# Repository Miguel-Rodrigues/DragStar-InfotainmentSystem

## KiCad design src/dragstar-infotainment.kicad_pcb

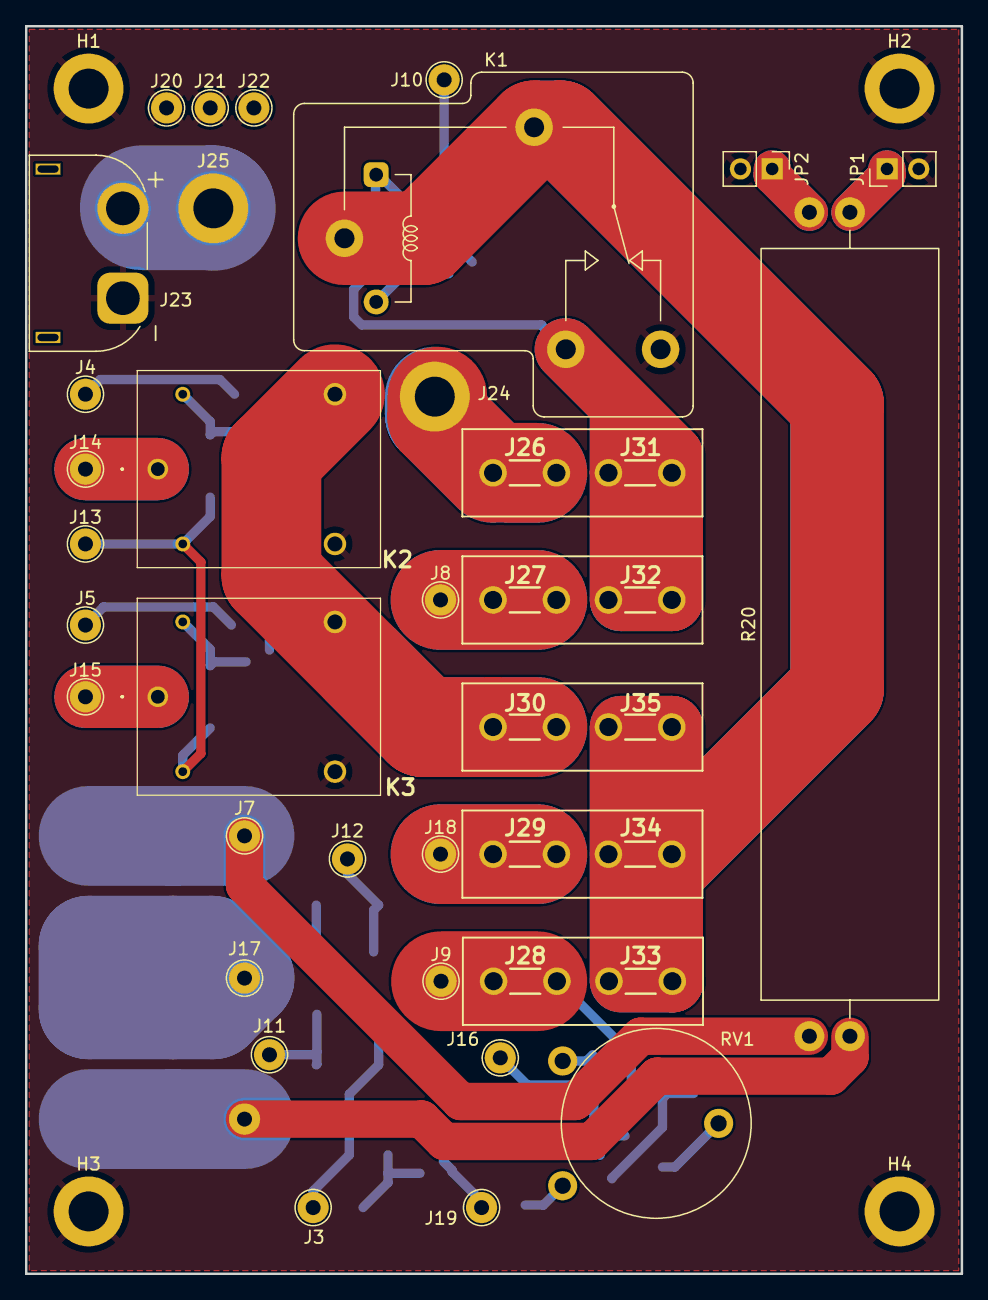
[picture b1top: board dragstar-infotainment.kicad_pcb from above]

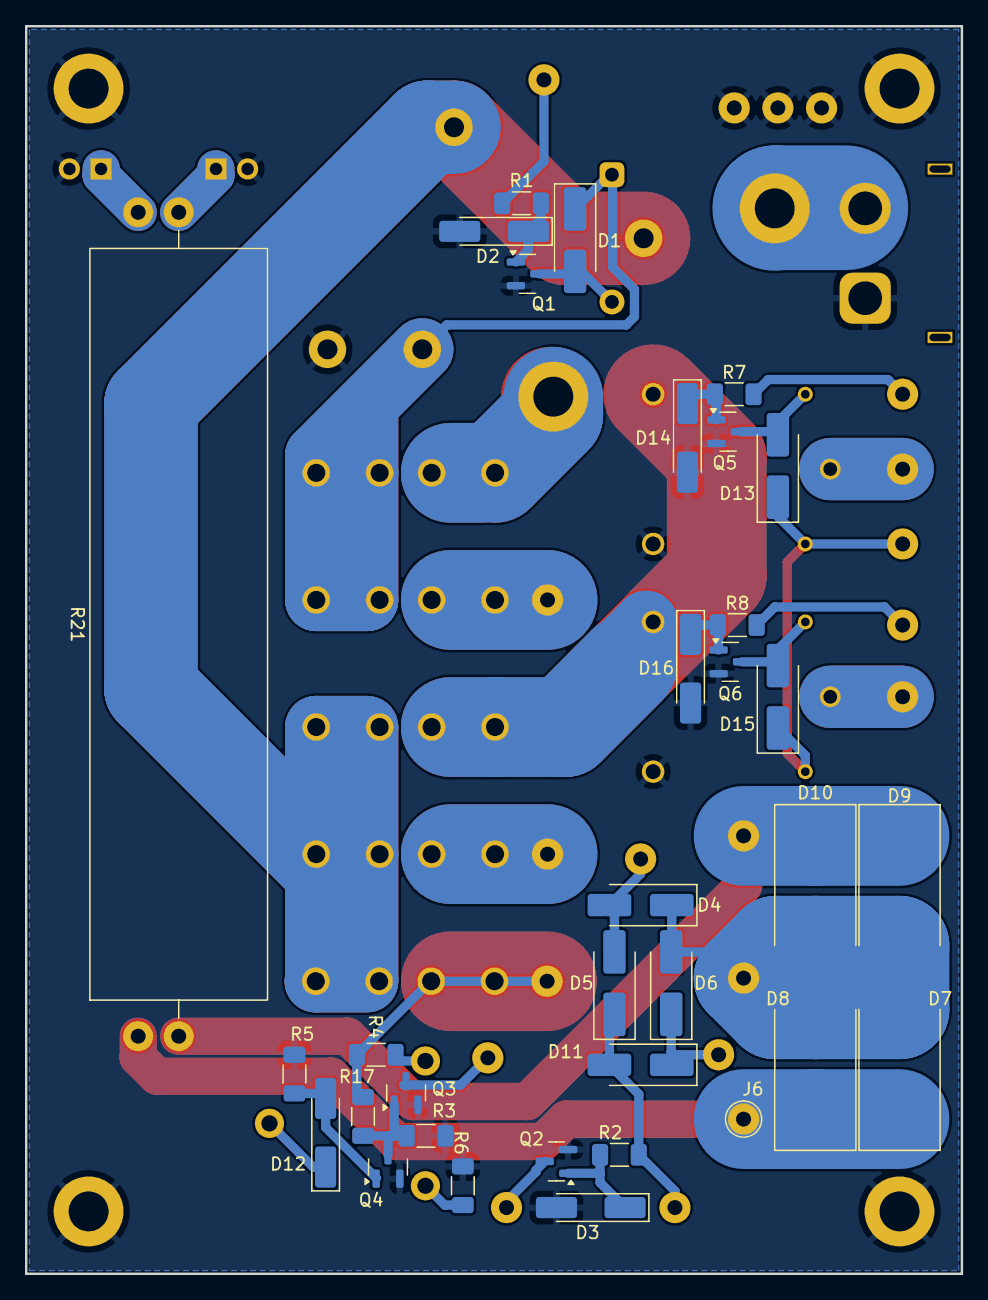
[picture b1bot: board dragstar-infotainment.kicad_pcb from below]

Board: 2 copper layers, 75.0 x 100.0 mm, 76 parts (33 on the bottom side), 37 nets.

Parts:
D1, D4, D5, D6, D11, D13, D15: US1M; D_SMA_Handsoldering
D2, D3, D12, D14, D16: BZV55C2V7; D_MiniMELF_Handsoldering
D7, D8, D9, D10: SK510; D_SMC_Handsoldering
H1, H2, H3, H4: MountingHole_Pad; MountingHole_3.2mm_M3_DIN965_Pad
J3, J4, J5, J6, J7, J8, J9, J10, J11, J12, J13, J14, J15, J16, J17, J18, J19, J20, J21, J22: Conn_01x01; TestPoint_THTPad_D2.5mm_Drill1.2mm
J23: XT60-M; AMASS_XT60PW-M_1x02_P7.20mm_Horizontal_Short
J24, J25: Conn_01x01; MountingHole_3.2mm_M3_DIN965_Pad
J26, J27, J28, J29, J30, J31, J32, J33, J34, J35: 1217080-1
JP1, JP2: Jumper_2_Bridged; PinHeader_1x02_P2.54mm_Vertical
K1: RAYEX-L90; Relay_SPDT_RAYEX-L90
K2, K3: LEG-12; LEG12
Q1, Q2, Q3, Q4, Q5, Q6: 2N7002; SOT-23
R1, R2, R3, R5, R7, R8: 10K; R_1206_3216Metric_Pad1.30x1.75mm_HandSolder
R4, R6, R17: 1.5K; R_1206_3216Metric_Pad1.30x1.75mm_HandSolder
R20, R21: 15W; R_Axial_Power_L60.0mm_W14.0mm_P66.04mm
RV1: 4.7K; Potentiometer_Piher_PT-15-V02_Vertical

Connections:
+12V: J33.1, J33.2, J34.1, J34.2, J35.1, J35.2, K1.11A, K1.11B
+BATT: J23.2, J25.1
AuxHBeam: J15.1, K3.COM
AuxLBeam: J14.1, K2.COM
AuxSwitch: D13.1 (K), D15.1 (K), J13.1, K2.A2, K3.A2
GND: D2.2 (A), D3.2 (A), D14.2 (A), D16.2 (A), H1.1, H2.1, H3.1, H4.1, J20.1, J21.1, J22.1, J23.1, JP1.2 (B), JP2.2 (B), K1.12, K2.NC, K3.NC, Q1.2 (S), Q2.2 (S), Q3.2 (S), Q4.2 (S), Q5.2 (S), Q6.2 (S), R3.1, R5.1, R6.1
GNDDash: J19.1, Q2.3 (D)
HBeam: J5.1, R8.1
Hazard: D4.1 (K), D6.2 (A), D7.2 (A), D8.2 (A), D9.2 (A), D10.2 (A), J17.1
HazardLed: D6.1 (K), D11.1 (K), J11.1
HazardLedReturn: D4.2 (A), D5.2 (A), J12.1
Key: J10.1, R1.1
Killswitch: J24.1, J26.1, J26.2
LBeam: J4.1, R7.1
LBlinker: D7.1 (K), D8.1 (K), J6.1, R20.1
LowBat: J16.1, Q3.3 (D)
MainRelay: D1.1 (K), J31.1, J31.2, J32.1, J32.2, K1.14, K1.A1
unnamed: D1.2 (A), K1.A2, Q1.3 (D)
unnamed: D2.1 (K), Q1.1 (G), R1.2
unnamed: D3.1 (K), Q2.1 (G), R2.2
unnamed: D12.2 (A), Q4.1 (G), R5.2
unnamed: D12.1 (K), RV1.2
unnamed: D13.2 (A), K2.A1, Q5.3 (D)
unnamed: D14.1 (K), Q5.1 (G), R7.2
unnamed: D15.2 (A), K3.A1, Q6.3 (D)
unnamed: D16.1 (K), Q6.1 (G), R8.2
unnamed: JP1.1 (A), R20.2
unnamed: JP2.1 (A), R21.2
unnamed: Q3.1 (G), Q4.3 (D), R3.2, R17.1
unnamed: R4.1, RV1.3
unnamed: R6.2, RV1.1
PLight: D5.1 (K), D11.2 (A), J3.1, R2.1
RBlinker: D9.1 (K), D10.1 (K), J7.1, R21.1
VAcc: J8.1, J27.1, J27.2
VInst: J9.1, J28.1, J28.2, R4.2, R17.2
VLight: J30.1, J30.2, K2.NO, K3.NO
VOutlet: J18.1, J29.1, J29.2

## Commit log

2023-07-10 Update Schematics design
2023-07-22 Update schematic design
2023-08-09 Add radio backup battery circuit; Update cable harness; rework main board circuit
2023-09-01 Update schematics
2024-02-17 Update Schmatics; Cleanup unecessary circuits; Simplify blinkers dimmers; Update PCB; Colorize motorcycle electric diagram.
2024-02-24 Update Schematics; Replace xor with quad nand; Update PCB
2024-02-24 update mini360 footprint
2024-03-06 Replace 7n2002 with IRLML0030 fo dimmer
2024-04-16 Update Design
2025-04-25 simplify circuit diagram. Remove unecessary features; Split board into two components|
2025-06-17 Simplify circuit diagram. Remove unecessary features
2025-06-20 Fix battery sensor
2025-06-21 Add LED Blinkers balasts; Update PCB
2025-06-24 Generate output files
2025-06-24 Update output files
2025-07-13 PCB Layout adjustments; generate new plots
